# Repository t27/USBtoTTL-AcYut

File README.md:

#USB to TTL Converter

This is a boar which converts USB to Half Duplex TTL(Serial). It is used for communicating with the Robotis Dynamixel line of motors. 

USB is converted to Serial using FTDI FT232RL and then to half duplex using a combinatino of Tri-State buffers.

Built for Team AcYut at CRIS, BITS Pilani.

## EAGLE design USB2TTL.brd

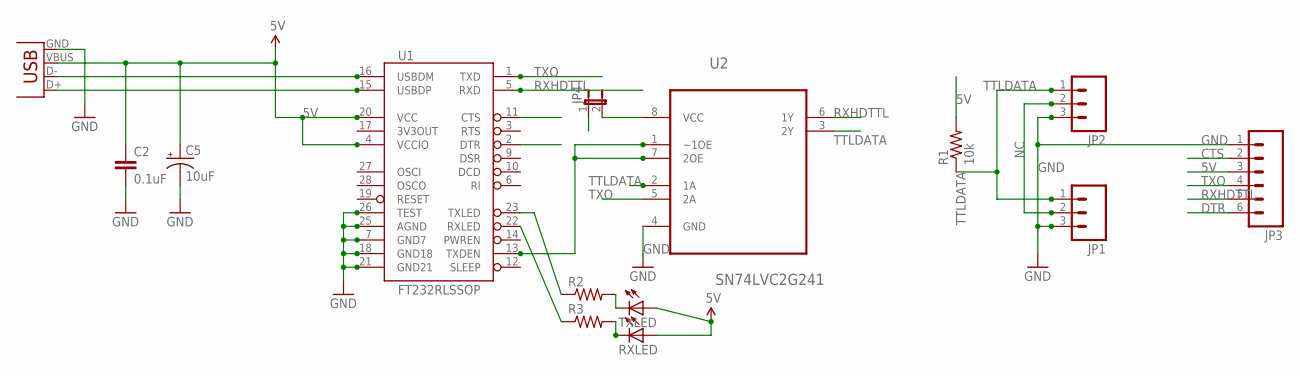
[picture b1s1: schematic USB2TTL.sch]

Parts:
C2: 0.1uF; 0402-CAP
C5: 10uF; EIA3216
JP1, JP2: M03LOCK_LONGPADS; 1X03_LOCK_LONGPADS
JP3: M06LOCK; 1X06_LOCK
JP4: JUMPER-2-OLDSMD-NO; SJ_2S-NO
R1: 10k; 0603-RES
R2, R3: RESISTOR0603-RES; 0603-RES
RXLED: LED0603; LED-0603
TXLED: LED0603; LED-0603
U1: FT232RLSSOP; SSOP28DB
U2: SN74LVC2G241; SOP65P400X130-8N
X2: USB-SMD-NS; USB-MINIB-NOSTOP

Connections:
5V: C2.1, C5.A (+), JP3.3, JP4.1, R1.2, RXLED.A, TXLED.A, U1.4 (VCCIO), U1.20 (VCC), X2.VBUS
CTS: JP3.2, U1.11 (CTS)
DTR: JP3.6, U1.2 (DTR)
GND: C2.2, C5.C (-), JP1.3, JP2.3, JP3.1, U1.7 (GND7), U1.18 (GND18), U1.21 (GND21), U1.25 (AGND), U1.26 (TEST), U2.4 (GND), X2.GND
unnamed: JP4.2, U2.8 (VCC)
unnamed: R2.1, U1.23 (TXLED)
unnamed: R3.1, U1.22 (RXLED)
unnamed: R2.2, TXLED.C
unnamed: R3.2, RXLED.C
NC: JP1.2, JP2.2
RXHDTTL: JP3.5, U1.5 (RXD), U2.6 (1Y)
TTLDATA: JP1.1, JP2.1, R1.1, U2.2 (1A), U2.3 (2Y)
TXDEN: U1.13 (TXDEN), U2.1 (~1OE), U2.7 (2OE)
TXO: JP3.4, U1.1 (TXD), U2.5 (2A)
USB_D+: U1.15 (USBDP), X2.D+
USB_D-: U1.16 (USBDM), X2.D-

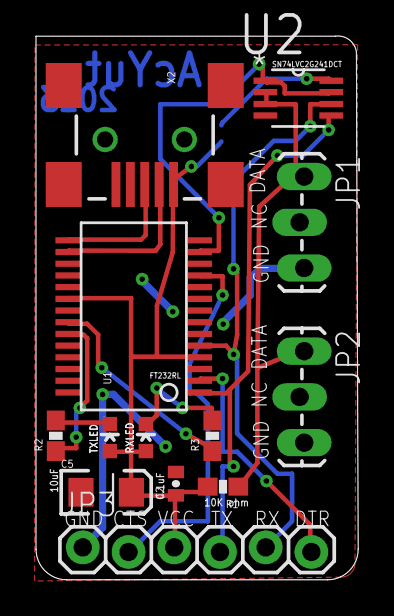
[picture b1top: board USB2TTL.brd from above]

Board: 2 copper layers, 17.9 x 30.2 mm, 14 parts (1 on the bottom side), 16 nets.

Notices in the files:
parts and their libraries:
SparkFun-Connectors: Licensing: CC v3.0 Share-Alike You are welcome to use this library for commercial purposes.
